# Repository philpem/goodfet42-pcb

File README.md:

GoodFET42 Modified PCB

This is a modified version of Travis Goodspeed's "GoodFET42" JTAG pod design.
The schematic has not been modified (except for renaming "LED1" to "MO" to
indicate its role as the Mode LED), but the PCB has been modified to allow it to
be built by hobbyists with a relatively modest home PCB lab.

Design rules are thus:

  * Top and bottom sides are linked by large vias, well away from ICs. This
    allows the top and bottom sides to be linked with Harwin track pins, pieces
    of solid-core wire, or similar things.
  * Tracks may enter SMD pads from the short side only, perpendicular with the
    long side (in other words: "make the pad longer"). This makes it easier to
    determine whether a short between two IC pins is intentional.
  * IDC connector is soldered on the bottom side only; tracks may connect from
    the bottom layer only. Most home PCB labs don't have through-plating
    facilities :)
  * 16 mil isolation from ground plane to tracks and pads.

Enjoy!

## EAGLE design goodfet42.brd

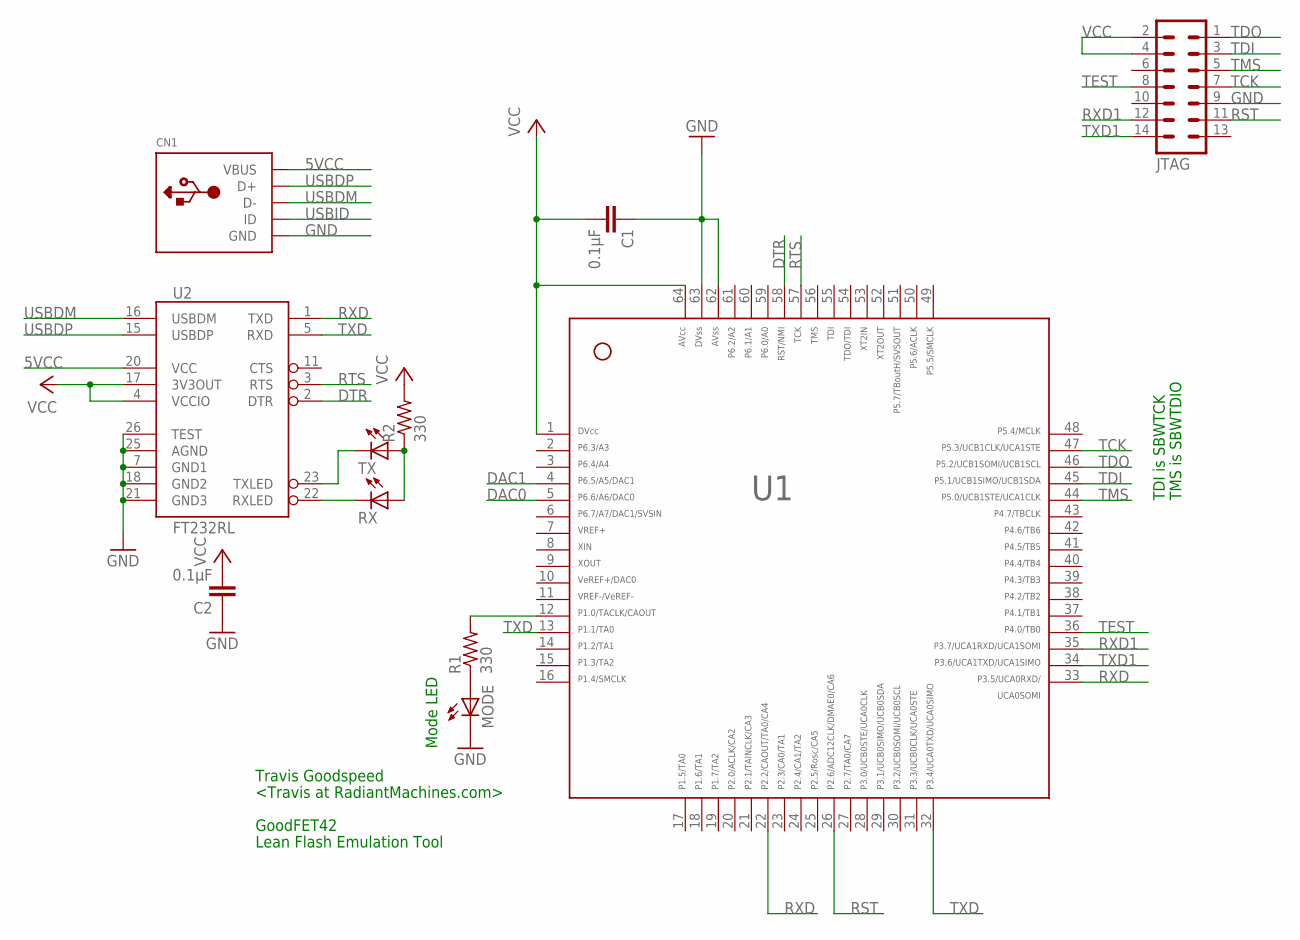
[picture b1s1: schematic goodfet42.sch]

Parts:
C1, C2: 0.1µF; C0603
CN1: USBMINIB; USB-MINIB
JTAG: MA07-2
MODE: LEDCHIP-LED0603; CHIP-LED0603
R1, R2: 330; R0603
RX: LEDCHIP-LED0603; CHIP-LED0603
TX: LEDCHIP-LED0603; CHIP-LED0603
U1: MSP430F2618TPM; PM/PAG64
U2: FT232RL; SSOP28DB

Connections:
5VCC: CN1.VBUS, U2.20 (VCC)
DAC0: U1.5
DAC1: U1.4
DTR: U1.58, U2.2 (DTR)
GND: C1.1, C2.1, CN1.GND, JTAG.9, MODE.C, U1.62, U1.63, U2.7 (GND1), U2.18 (GND2), U2.21 (GND3), U2.25 (AGND), U2.26 (TEST)
unnamed: R1.2, U1.12
unnamed: MODE.A, R1.1
unnamed: RX.C, U2.22 (RXLED)
unnamed: TX.C, U2.23 (TXLED)
unnamed: R2.1, RX.A, TX.A
RST: JTAG.11, U1.26
RTS: U1.57, U2.3 (RTS)
RXD: U1.22, U1.33, U2.1 (TXD)
RXD1: JTAG.12, U1.35
TCK: JTAG.7, U1.47
TDI: JTAG.3, U1.45
TDO: JTAG.1, U1.46
TEST: JTAG.8, U1.36
TMS: JTAG.5, U1.44
TXD: U1.13, U1.32, U2.5 (RXD)
TXD1: JTAG.14, U1.34
USBDM: CN1.D-, U2.16 (USBDM)
USBDP: CN1.D+, U2.15 (USBDP)
USBID: CN1.ID
VCC: C1.2, C2.2, JTAG.2, JTAG.4, R2.2, U1.1, U1.64, U2.4 (VCCIO), U2.17 (3V3OUT)

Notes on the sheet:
TDI is SBWTCK
TMS is SBWTDIO
Mode LED
Travis Goodspeed
<Travis at RadiantMachines.com>
GoodFET42
Lean Flash Emulation Tool

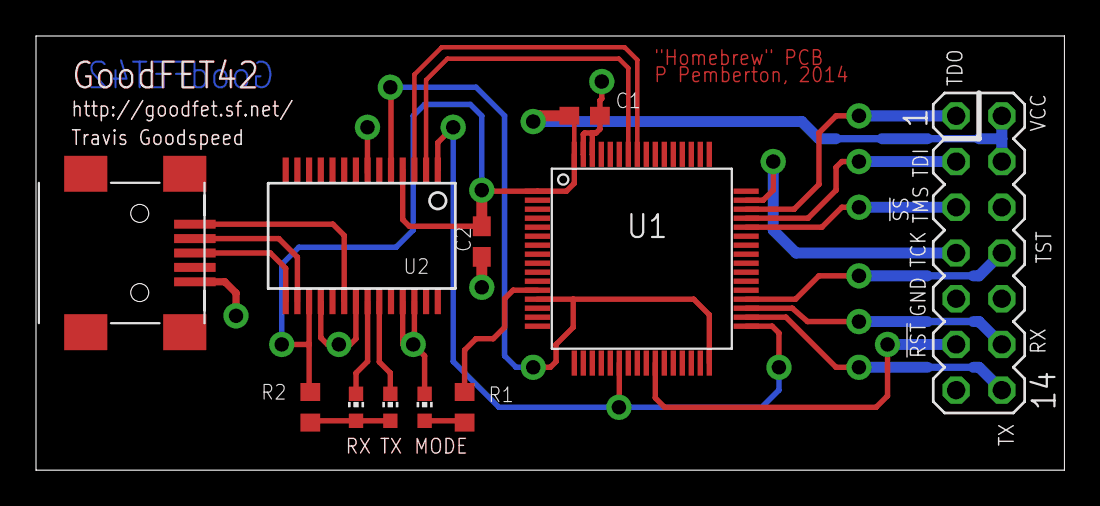
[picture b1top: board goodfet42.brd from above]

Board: 2 copper layers, 57.1 x 24.1 mm, 11 parts (0 on the bottom side), 22 nets.

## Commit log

2014-02-14 Commit modified GoodFET42 board, tweaked for home etching
2014-02-14 Add README.md
2014-02-15 rename MO LED to MODE, silkscreen fixes, add Homebrew PCB designation
2014-02-16 add 'GoodFET42' text on bottom layer to help with board alignment
